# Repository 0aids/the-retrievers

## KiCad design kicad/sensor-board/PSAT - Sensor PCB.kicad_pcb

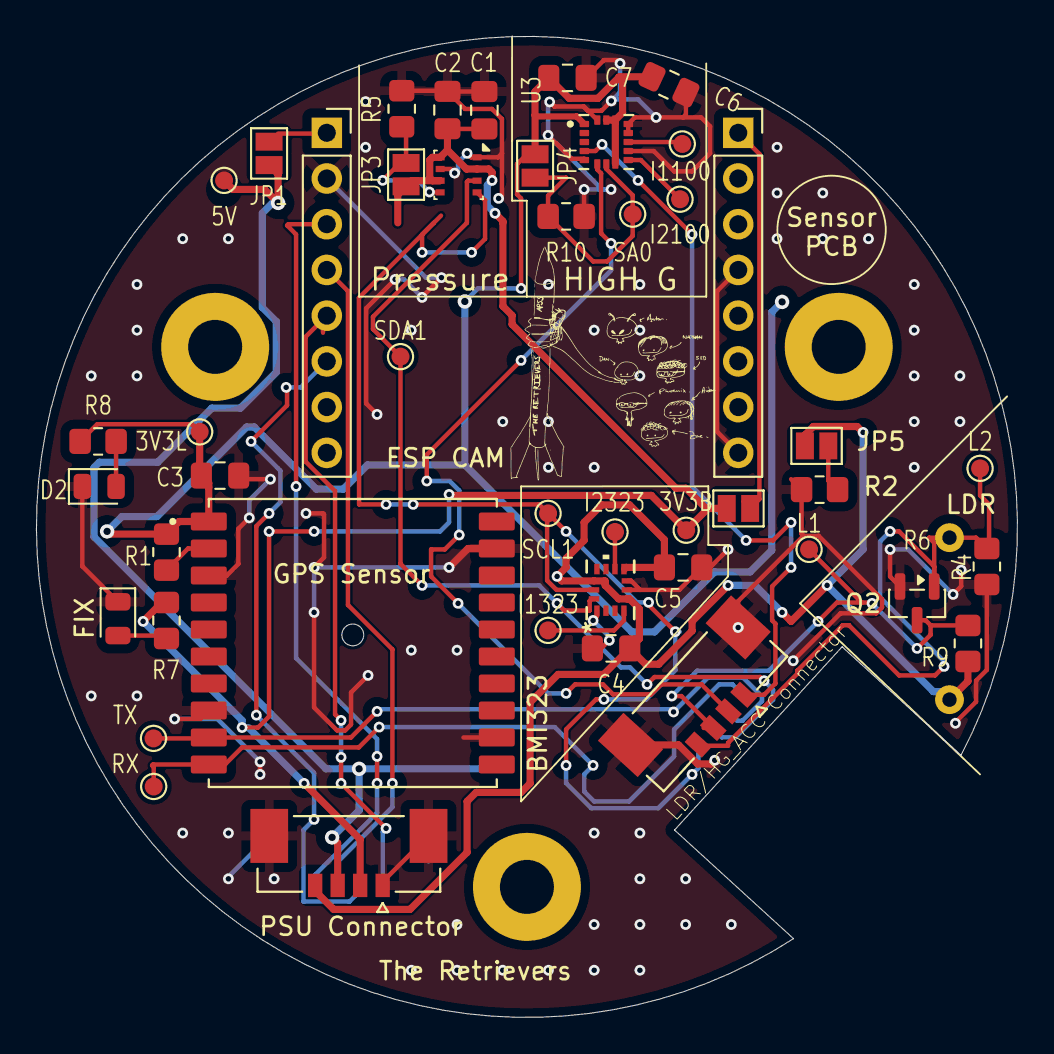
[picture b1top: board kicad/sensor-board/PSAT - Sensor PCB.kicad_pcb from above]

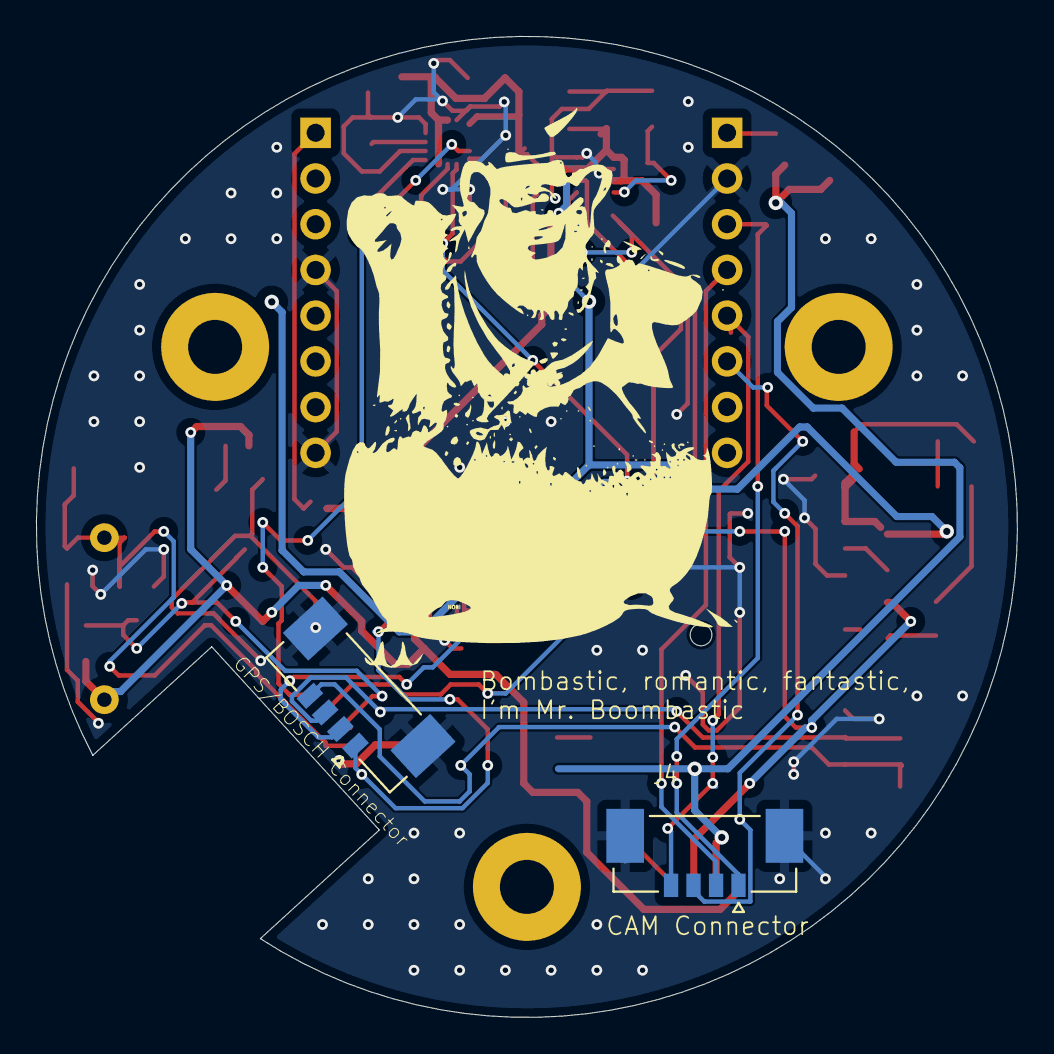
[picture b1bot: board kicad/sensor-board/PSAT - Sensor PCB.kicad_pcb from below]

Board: 2 copper layers, 54.5 x 54.5 mm, 50 parts (2 on the bottom side), 28 nets.

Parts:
3V3B, 3V3L, 5V: TestPoint; TestPoint_Pad_D1.0mm
C1, C2, C4, C5, C7: 100nF; C_0805_2012Metric_Pad1.18x1.45mm_HandSolder
C3: 22uF; C_0805_2012Metric_Pad1.18x1.45mm_HandSolder
C6: 10uF; C_0805_2012Metric_Pad1.18x1.45mm_HandSolder
D1, D2: LED; LED_0805_2012Metric
H1, H2, H3: MountingHole; MountingHole_3mm_Pad
I1100, I1323, I2100, I2323: TestPoint; TestPoint_Pad_D1.0mm
J1, J2, J3, J4: 533980471; MOLEX_533980471
JP1, JP2, JP3, JP4, JP5: EN_5; SolderJumper-2_P1.3mm_Open_Pad1.0x1.5mm
L1, L2: TestPoint; TestPoint_Pad_D1.0mm
Q2: Q_NPN_BEC; SOT-23
R1: 10k; R_0805_2012Metric_Pad1.20x1.40mm_HandSolder
R2, R5, R10: 1Meg; R_0805_2012Metric_Pad1.20x1.40mm_HandSolder
R4: 3.7k; R_0805_2012Metric_Pad1.20x1.40mm_HandSolder
R6: LDR07; ldr
R7, R8: 5.1k; R_0805_2012Metric_Pad1.20x1.40mm_HandSolder
R9: 100k; R_0805_2012Metric_Pad1.20x1.40mm_HandSolder
RX: TestPoint; TestPoint_Pad_D1.0mm
SA0: TestPoint; TestPoint_Pad_D1.0mm
SCL1: TestPoint; TestPoint_Pad_D1.0mm
SDA1: TestPoint; TestPoint_Pad_D1.0mm
TX: TestPoint; TestPoint_Pad_D1.0mm
U1: CD-PA1616D; XCVR_CD-PA1616D
U2: ESP32-CAM; ESPCam
U3: BME280; Bosch_LGA-8_2.5x2.5mm_P0.65mm_ClockwisePinNumbering
U4: BMI323; BMI323_BOS-M
U5: H3LIS100DLTR; PQFN50P300X300X100-16N

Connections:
3V3_BUCK: 3V3B.1, C1.2, C2.1, J3.2, JP2.1 (A), JP3.1 (A), R7.1, U3.2 (CSB), U3.6 (VDDIO), U3.8 (VDD)
3V3_LDO: 3V3L.1, C3.1, C4.2, C5.1, C6.1, C7.1, J3.4, JP4.1 (A), JP5.1 (A), R1.1, R6.1, R8.1, R9.2, U1.1 (VCC), U4.5 (VDDIO), U4.8 (VDD), U4.12 (CSB), U5.1 (VDD_IO), U5.8 (CS), U5.14 (VDD), U5.15 (VDD__1)
5V: 5V.1, J3.3, JP1.1 (A)
CAM_IO14: J4.3, U2.6 (IO14)
CAM_IO15: J4.4, U2.5 (IO15)
CAM_RX: J4.1, U2.3 (IO12)
CAM_TX: J4.2, U2.4 (IO13)
GND: C1.1, C2.2, C3.2, C4.1, C5.2, C6.2, C7.2, D1.1 (K), D2.1 (K), J1.S1 (SHIELD1), J1.S2 (SHIELD2), J2.S1 (SHIELD1), J2.S2 (SHIELD2), J3.1, J3.S1 (SHIELD1), J3.S2 (SHIELD2), J4.S1 (SHIELD1), J4.S2 (SHIELD2), Q2.2 (E), R2.2, R4.1, R5.2, R10.2, U1.3 (GND), U1.8 (GND), U1.12 (GND), U1.19 (GND), U2.2 (GND), U2.12 (GND.), U2.16 (.GND), U3.1 (GND), U3.7 (GND), U4.1 (SDO), U4.6 (GNDIO), U4.7 (GND), U5.5 (GND), U5.10 (GND__1), U5.12 (GND__2), U5.13 (GND__3), U5.16 (GND__4)
GPS_UART_RX: J2.4, RX.1, U1.10 (RX)
GPS_UART_TX: J2.3, TX.1, U1.9 (TX)
IN2_100: I2100.1, U5.9 (INT2)
INT1_100: I1100.1, U5.11 (INT1)
INT1_323: I1323.1, U4.4 (INT1)
INT2_323: I2323.1, U4.9 (INT2)
LIGHT1: J1.3, L1.1, Q2.3 (C), R9.1
LIGHT2: J1.4, L2.1, Q2.1 (B), R4.2, R6.2
unnamed: D1.2 (A), R7.2
unnamed: D2.2 (A), R8.2
unnamed: JP1.2 (B), U2.1 (5V)
unnamed: JP2.2 (B), U2.9 (3V3)
unnamed: R1.2, U1.2 (~RESET)
PRESSURE_ADDR: JP3.2 (B), R5.1, U3.5 (SDO)
SA0: JP4.2 (B), R10.1, SA0.1, U5.7 (SDO/SA0)
SCL1: J2.1, SCL1.1, U3.4 (SCK), U4.13 (SCX)
SCL2: J1.1, U5.4 (SCL/SPC)
SDA1: J2.2, SDA1.1, U3.3 (SDI), U4.14 (SDX)
SDA2: J1.2, U5.6 (SDA/SDI/SDO)
SDO: JP5.2 (B), R2.1

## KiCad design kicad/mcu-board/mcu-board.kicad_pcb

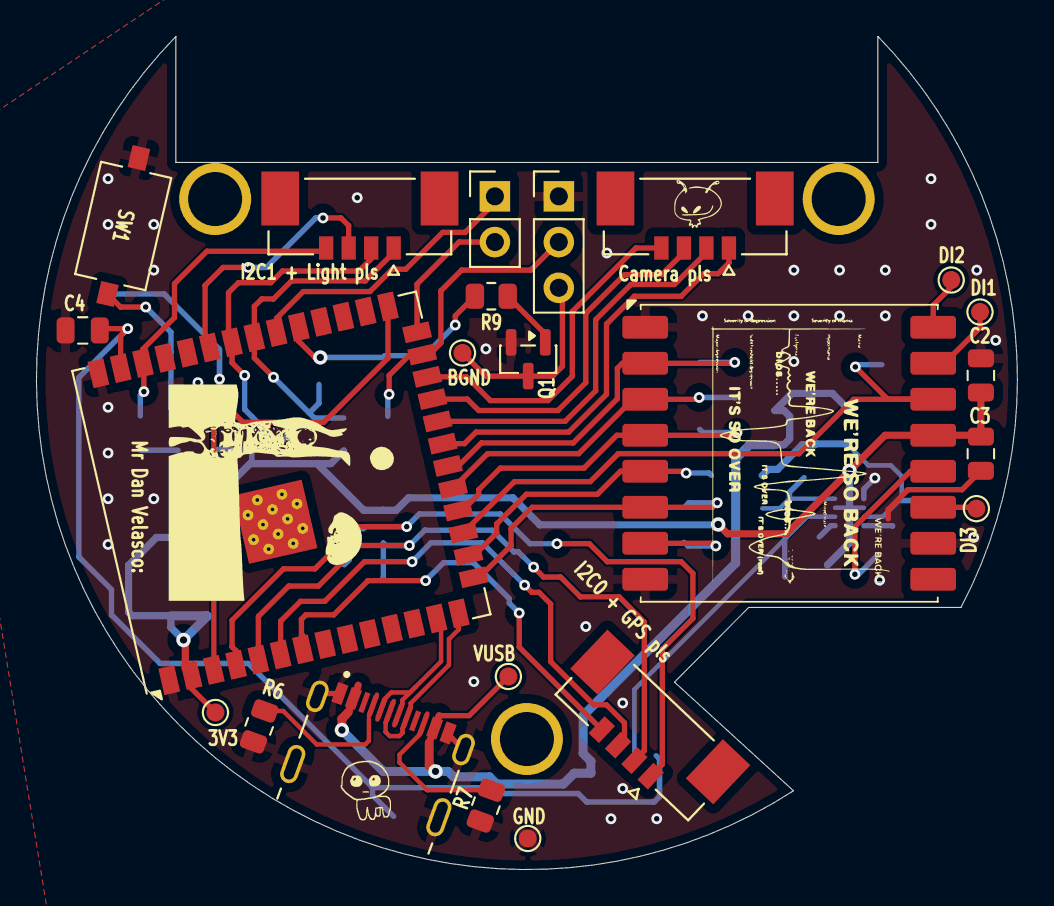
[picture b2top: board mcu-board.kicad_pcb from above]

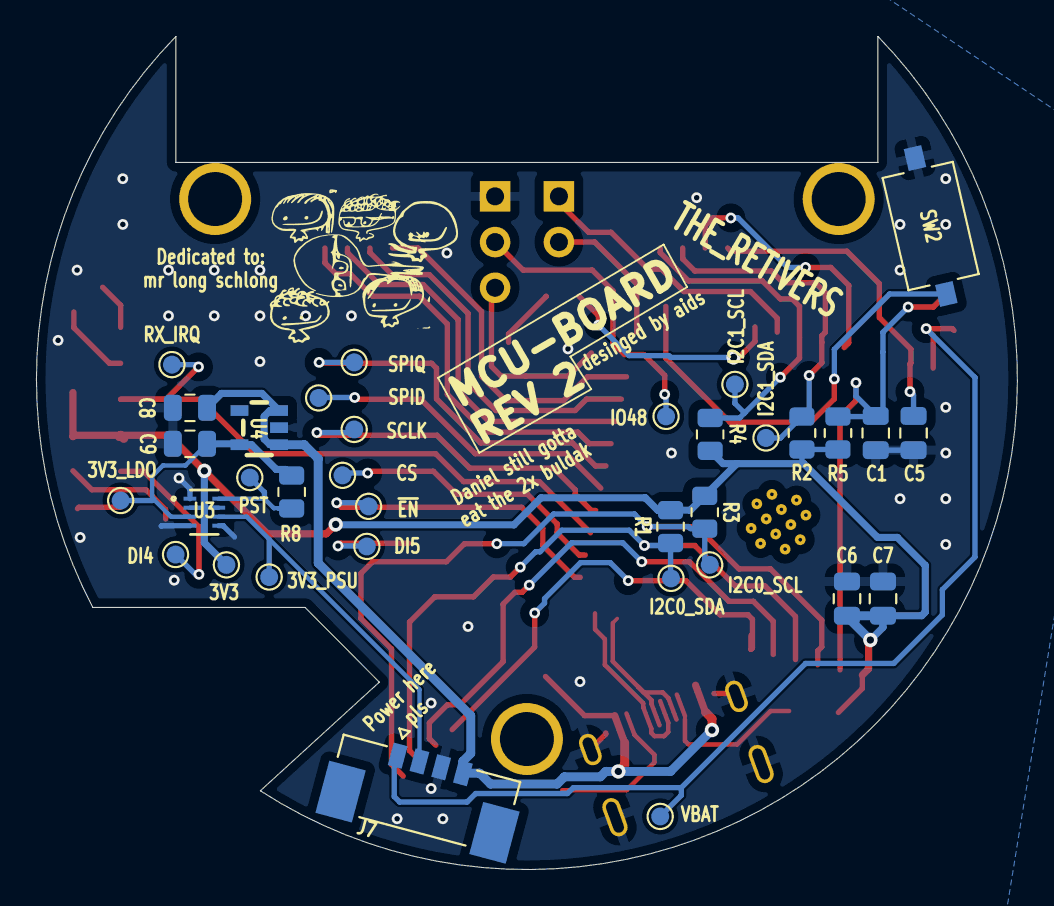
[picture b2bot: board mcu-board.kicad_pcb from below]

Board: 2 copper layers, 54.5 x 46.3 mm, 60 parts (34 on the bottom side), 42 nets.

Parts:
C1: 1uf; C_0805_2012Metric
C2, C6: 22uf; C_0805_2012Metric
C3, C4, C5, C7: 0.1uf; C_0805_2012Metric
C8, C9: 1u; C_0805_2012Metric
H1, H2, H3: MountingHole; Mounting-Hole-3mm-0.05mm-pad
J1: Conn_01x03; PinHeader_1x03_P2.54mm_Vertical
J2: Conn_01x02; PinHeader_1x02_P2.54mm_Vertical
J3, J4, J5, J7: 533980471; MOLEX_533980471
J6: UJ20-C-H-G-SMT-P16-TR; SAMESKY_UJ20-C-H-G-SMT-P16-TR
Q1: MMBT619; SOT-23
R1, R2, R3, R4, R6, R7, R8: 5.1k; R_0805_2012Metric
R5, R9: 10k; R_0805_2012Metric
SW1, SW2: SW_Push; SW_Tactile_SPST_NO_Straight_CK_PTS636Sx25SMTRLFS
TP1, TP2, TP3, TP4, TP5, TP6, TP7, TP8, TP9, TP10, TP11, TP12, TP13, TP14, TP15, TP15#2, TP16, TP17, TP18, TP19, TP20, TP21, TP22, TP23: TestPoint; TestPoint_Pad_D1.0mm
U1: Lora1276-C1-868
U2: ESP32-S3-WROOM-1U-N16R8; ESP32-S3-WROOM-1U
U3: LM66200DRLR; SOT-5X3_DRL_TEX
U4: TLV75733PDBVR
VBAT1: TestPoint; TestPoint_Pad_D1.0mm

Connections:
+3V3: C2.1, C3.1, C6.1, C7.1, R1.2, R2.2, R3.1, R4.1, R5.2, TP15.1, TP19.1, U1.13 (VCC), U2.2 (3V3), U3.2 (VOUT), U3.7 (VOUT)
+3V3_LDO_LOCAL: C9.2, R8.1, TP21.1, U3.3 (VIN1), U4.5 (OUT)
+3V3_PSU_LDO: J7.2, TP22.1, U3.6 (VIN2)
/BUZZER_IO38: R9.1, U2.31 (IO38)
/CAM_IO13: J5.1, U2.21 (IO13)
/CAM_IO14: J5.2, U2.22 (IO14)
/CAM_IO21: J5.3, U2.23 (IO21)
/CAM_IO47: J5.4, U2.24 (IO47)
/D+: J6.A6 (DP1), J6.B6 (DP2), U2.14 (IO20)
/D-: J6.A7 (DN1), J6.B7 (DN2), U2.13 (IO19)
/DI1: TP11.1, U1.15 (DI1)
/DI2: TP12.1, U1.16 (DI2)
/DI3: TP13.1, U1.11 (DI3)
/DI4: TP14.1, U1.12 (DI4)
/DI5: TP15#2.1, U1.7 (DI5)
/ESP_RESET: C1.1, R5.1, SW1.2, U2.3 (EN)
/GPS_U1RX_IO7: J3.4, U2.7 (IO7)
/GPS_U1TX_IO6: J3.3, U2.6 (IO6)
/I2C0_SCL_IO4: J3.1, R3.2, TP4.1, U2.4 (IO4)
/I2C0_SDA_IO5: J3.2, R1.1, TP2.1, U2.5 (IO5)
/I2C1_SCL_IO40: J4.1, R4.2, TP5.1, U2.33 (IO40)
/I2C1_SDA_IO41: J4.2, R2.1, TP3.1, U2.34 (IO41)
/IO39: J2.1, U2.32 (IO39)
/IO45: J2.2, U2.26 (IO45)
/LIGHT_1_IO42: J4.3, U2.35 (IO42)
/LIGHT_2_ADC1CH1_IO2: C5.2, J4.4, U2.38 (IO2)
/LORA_IRQ_IO9: TP16.1, U1.14 (DI0), U2.17 (IO9)
/LORA_SPI3_CLK_IO10: TP9.1, U1.4 (SCK), U2.18 (IO10)
/LORA_SPI3_CS_IO46: TP10.1, U1.5 (~SS), U2.16 (IO46)
/LORA_SPI3_D_IO11: TP8.1, U1.3 (MOSI), U2.19 (IO11)
/LORA_SPI3_Q_IO12: TP7.1, U1.2 (MISO), U2.20 (IO12)
/Power Management/POWER_ST: R8.2, TP20.1, U3.8 (ST)
/SERVO_IO48: J1.2, TP6.1, U2.25 (IO48)
/VBAT_IO1: C4.1, J7.1, U2.39 (IO1), VBAT1.1
/~LORA_EN_IO3: TP1.1, U1.6 (~RESET), U2.15 (IO3)
BUZ_GND: J1.3, Q1.3 (C), TP23.1
GND: C1.2, C2.2, C3.2, C4.2, C5.1, C6.2, C7.2, C8.1, C9.1, J1.1, J6.A1_B12 (GND), J6.A12_B1 (GND__1), J6.SH1 (SHIELD), J6.SH2 (SHIELD__1), J6.SH3 (SHIELD__2), J6.SH4 (SHIELD__3), J7.3, Q1.2 (E), R6.1, R7.1, SW1.1, SW2.1, TP18.1, U1.1 (GND), U1.8 (GND), U1.10 (GND), U2.1 (GND), U2.40 (GND), U3.1 (GND), U3.4 (~ON), U3.5 (GND), U4.2 (GND)
unnamed: J6.A5 (CC1), R6.2
unnamed: J6.B5 (CC2), R7.2
unnamed: Q1.1 (B), R9.2
unnamed: SW2.2, U2.27 (IO0)
V_USB: C8.2, J6.A4_B9 (VBUS), J6.A9_B4 (VBUS__1), J7.4, TP17.1, U4.1 (IN), U4.3 (EN)

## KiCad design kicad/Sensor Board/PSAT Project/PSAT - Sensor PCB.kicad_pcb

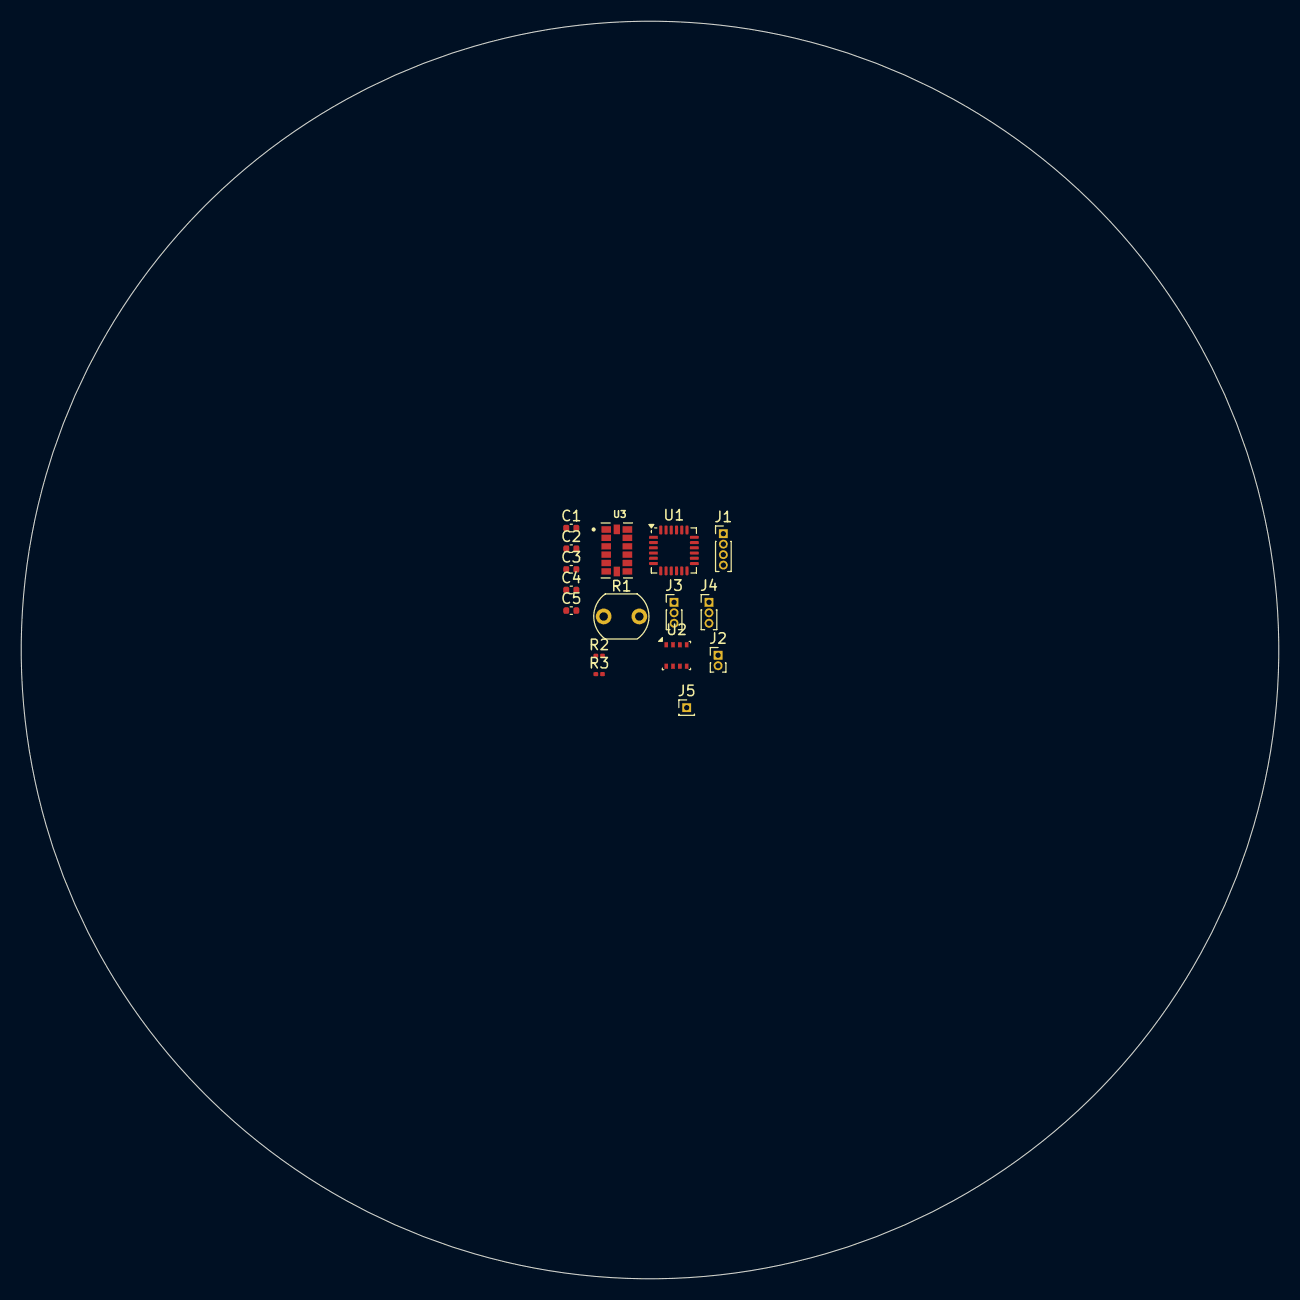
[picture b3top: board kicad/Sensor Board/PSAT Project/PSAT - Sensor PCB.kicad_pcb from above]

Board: 2 copper layers, 120.0 x 120.0 mm, 16 parts (0 on the bottom side), 16 nets, no tracks yet.

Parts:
C1: 2.2n; C_0402_1005Metric
C2: 0.1n; C_0402_1005Metric
C3: 0.1μ; C_0402_1005Metric
C4, C5: 100n; C_0402_1005Metric
J1: MCU Conn_01x04; PinHeader_1x04_P1.00mm_Vertical
J2: Conn_01x02; PinHeader_1x02_P1.00mm_Vertical
J3, J4: Conn_01x03; PinHeader_1x03_P1.00mm_Vertical
J5: Conn_01x01; PinHeader_1x01_P1.00mm_Vertical
R1: LDR07; R_LDR_5.1x4.3mm_P3.4mm_Vertical
R2, R3: 4.7k; R_0201_0603Metric
U1: MPU-6000; InvenSense_QFN-24_4x4mm_P0.5mm
U2: BME280; Bosch_LGA-8_2.5x2.5mm_P0.65mm_ClockwisePinNumbering
U3: PQFN80P500X300X100-14N

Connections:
+3.3V: C2.1, C4.1, R1.1, U1.8 (~CS), U1.13 (VDD), U2.8 (VDD), U3.3 (RESERVED), U3.6 (Vs)
GND: C1.1, C2.2, C3.1, C4.2, C5.2, J5.1, R1.2, U1.1 (CLKIN), U1.11 (FSYNC), U1.18 (GND), U2.1 (GND), U2.5 (SDO), U2.7 (GND), U3.2 (GND), U3.4 (GND), U3.5 (GND), U3.11 (RESERVED), U3.12 (SDO/ALT_ADDRESS)
unnamed: J1.1, U1.23 (SCL/SCLK)
unnamed: J1.2, U1.9 (AD0/MISO)
unnamed: J1.3, U1.24 (SDA/MOSI)
unnamed: J1.4, U1.12 (INT)
unnamed: C5.1, J2.1, J2.2, R2.1, R3.1, U2.3 (SDI), U2.4 (SCK), U2.6 (VDDIO)
unnamed: J3.1, U3.8 (INT1)
unnamed: J3.2, U3.9 (INT2)
unnamed: J3.3, U3.10 (NC)
unnamed: J4.1, U3.14 (SCL/SCLK)
unnamed: J4.2, U3.13 (SDA/SDI/SDIO)
unnamed: J4.3, U3.7 (CS)
unnamed: C1.2, U1.20 (CPOUT)
unnamed: C3.2, U1.10 (REGOUT)
unnamed: R2.2, R3.2, U2.2 (CSB)

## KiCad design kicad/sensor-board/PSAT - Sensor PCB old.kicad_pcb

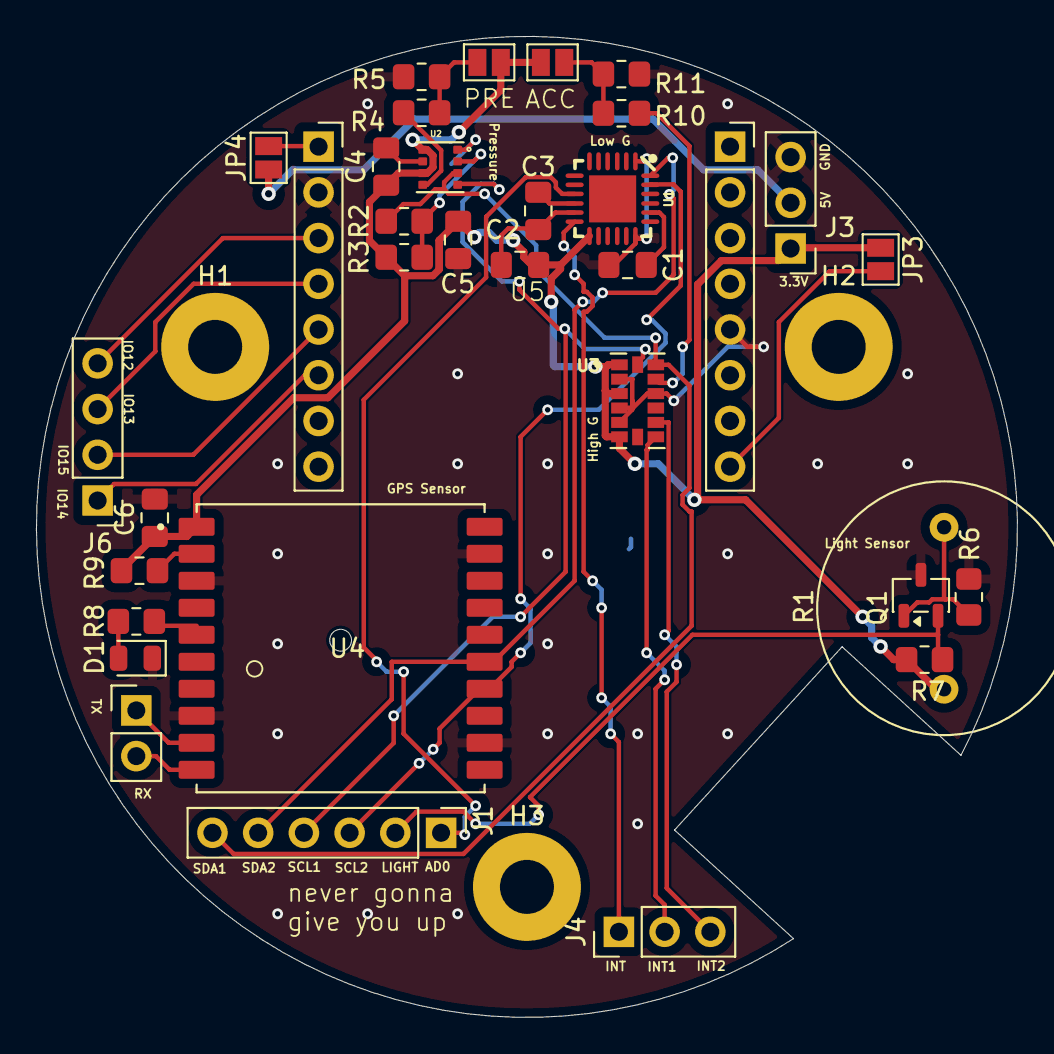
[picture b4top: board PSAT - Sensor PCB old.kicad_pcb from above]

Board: 2 copper layers, 54.5 x 54.5 mm, 36 parts (0 on the bottom side), 31 nets.

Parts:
C1: 2.2n; C_0805_2012Metric_Pad1.18x1.45mm_HandSolder
C2: 0.1n; C_0805_2012Metric_Pad1.18x1.45mm_HandSolder
C3: 0.1μ; C_0805_2012Metric_Pad1.18x1.45mm_HandSolder
C4, C5: 100n; C_0805_2012Metric_Pad1.18x1.45mm_HandSolder
C6: 22uF; C_0805_2012Metric_Pad1.18x1.45mm_HandSolder
D1: LED; LED_0805_2012Metric
H1, H2, H3: MountingHole; MountingHole_3mm_Pad
J1: Conn_01x06; PinHeader_1x06_P2.54mm_Vertical
J2: Conn_01x02; PinHeader_1x02_P2.54mm_Vertical
J3: Conn_01x03_Pin; PinHeader_1x03_P2.54mm_Vertical
J4: Conn_01x03; PinHeader_1x03_P2.54mm_Vertical
J6: MCU - Conn_01x04; PinHeader_1x04_P2.54mm_Vertical
JP1, JP2, JP3, JP4: EN_5; SolderJumper-2_P1.3mm_Open_Pad1.0x1.5mm
Q1: Q_NPN_BCE; SOT-23-3
R1: LDR07; R_LDR_D13.8mm_P9.0mm_Vertical
R2, R3: 4.7k; R_0805_2012Metric_Pad1.20x1.40mm_HandSolder
R4, R10: 1k5; R_0805_2012Metric_Pad1.20x1.40mm_HandSolder
R5, R11: 1Meg; R_0805_2012Metric_Pad1.20x1.40mm_HandSolder
R6, R7: 10k; R_0805_2012Metric_Pad1.20x1.40mm_HandSolder
R8: 1k; R_0805_2012Metric_Pad1.20x1.40mm_HandSolder
R9: 180k; R_0805_2012Metric_Pad1.20x1.40mm_HandSolder
U1: MPU-6000; QFN-24-EP
U2: BME280; PSON65P250X250X100-8N
U3: ADXL375; PQFN80P500X300X100-14N
U4: CD-PA1616D; XCVR_CD-PA1616D
U5: ESP32-CAM; ESPCam

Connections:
3.3V: C2.1, C4.1, C5.1, C6.1, J3.1, JP1.1 (A), JP2.1 (A), JP3.1 (A), R1.1, R3.1, R7.2, R9.1, U1.13 (VDD), U2.6 (VDDIO), U2.8 (VDD), U3.1 (VDD_I/o), U3.3 (RESERVED), U3.6 (Vs), U4.1 (VCC)
5V: J3.2, JP4.1 (A)
/GPS Reset: R9.2, U4.2 (~RESET)
ADO: J1.1, U1.9 (AD0/MISO)
GND: C1.1, C2.2, C3.1, C4.2, C5.2, C6.2, D1.1 (K), J3.3, Q1.3 (E), R5.2, R6.1, R11.2, U1.1 (CLKIN), U1.11 (FSYNC), U1.18 (GND), U2.1 (GND), U2.7 (GND), U3.2 (GND), U3.4 (GND), U3.5 (GND), U3.11 (RESERVED), U4.3 (GND), U4.8 (GND), U4.12 (GND), U4.19 (GND), U5.2 (GND), U5.13 (GND.)
GPS_UART_RX: J2.2, U4.10 (RX)
GPS_UART_TX: J2.1, U4.9 (TX)
INT: J4.1, U1.12 (INT)
LIGHT: J1.2, Q1.2 (C), R7.1
unnamed: D1.2 (A), R8.2
unnamed: J4.2, U3.8 (INT1)
unnamed: J4.3, U3.9 (INT2)
unnamed: J6.1, U5.6 (IO14)
unnamed: J6.2, U5.5 (IO15)
unnamed: J6.3, U5.4 (IO13)
unnamed: J6.4, U5.3 (IO12)
unnamed: JP1.2 (B), R4.2, R5.1
unnamed: JP2.2 (B), R10.2, R11.1
unnamed: JP3.2 (B), U5.16 (3V3)
unnamed: JP4.2 (B), U5.1 (5V)
unnamed: Q1.1 (B), R1.2, R6.2
unnamed: C1.2, U1.20 (CPOUT)
unnamed: C3.2, U1.10 (REGOUT)
unnamed: R2.2, R3.2, U2.2 (CSB)
unnamed: R8.1, U4.5 (3D-FIX)
SCL1: J1.4, U2.4 (SCK), U3.14 (SCL/SCLK)
SCL2: J1.3, U1.23 (SCL/SCLK), U4.14 (RX1/I2C_SCL)
SDA1: J1.6, R2.1, U2.3 (SDI), U3.13 (SDA/SDI/SDIO)
SDA2: J1.5, U1.24 (SDA/MOSI), U4.15 (TX1/I2C_SDA)
SDO_ACC: R10.1, U3.12 (SDO/ALT_ADDRESS)
SDO_PRESSURE: R4.1, U2.5 (SDO)

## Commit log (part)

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2026-01-13 feat: reuseable button component
2026-01-13 chore: rename lowpwr to lowPower, just looked weird
2026-01-13 chore: update cspell ignore list
2026-01-13 chore: use uart num from config for gps
2026-01-14 feat: new deployPending state
2026-01-14 feat: add task to check ADC to confirm deployment
2026-01-14 feat: buzzer working
2026-01-14 fix: include if global event in config for timer
2026-01-15 refactor: ldr.c & ldr.h are now in the code style Aiden sent
2026-01-15 fix: removed the static variables adcRaw & voltage while removing the 2d matrix.
2026-01-15 style: Added comments to ldr.h
2026-01-17 chore: update baud rate for new gps chip
2026-01-17 fix: Fixed some syntax erorrs and reverted changes in psat station
2026-01-17 test: Added preflight tests for both ldr and battery
2026-01-18 feat: convert shared/ into a esp component This is so that we can use shared_state.c in any component
2026-01-18 chore: update currentState_s to use psat_globalState.currentFSMState
2026-01-18 feat: simple buzzer beep test
2026-01-18 test: buzzer gpio pin goes HIGH during beep
2026-01-18 test: add tests for the servo
2026-01-18 chore: moved the idf.py flakes to the relevant psat-station subproject
2026-01-18 feat: added the shared_lora as a component named "lora"
2026-01-18 refac: Separated lora config from loraImpl.h into loraCfg.h.
2026-01-18 revert: "feat: update gpsData_s to psat_globalState.gpsData"
    This reverts commit 50d5446f3d3b955fb7a0421dd1cfc662480110d1.
2026-01-18 fix: precommit to work without using espidf terminal
2026-01-19 revert: undid some formatting done at 8f58e9f3.
2026-01-19 chore: added ai disclosure for tests
2026-01-19 fix: Added proper error handling, will add some checker in the implementation later
2026-01-19 feat: add entry, exit handlers for each state
2026-01-19 test: added the files for testing ldr
2026-01-19 feat: actually update the entry/exit handlers to contain what used to be in state_handlers.c
2026-01-19 feat: added the tests for ldr and made sure it builds
2026-01-19 fix: istg I pushed this and it fucking disappeared - fixed precommit
2026-01-21 fix(#13): Stop using goofy struct for config and just use #define And also format everything
2026-01-21 chore: remove random main.c file
2026-01-21 fix: reduced stack usage by decreasing default packet size. Will switch to heap allocation later.
    no more stack overflows now
2026-01-21 fix: for some reason was using a copy of shared_lora.h, not a symlink.
2026-01-21 feat: implemented internal use dynamic memory allocation for loraFsm.
2026-01-22 fix: clashing gpio_install_isr_service between lora and buttons. Moved to prelaunch entry handler
2026-01-22 refactor: moved configuration of ldr and renamed unclear variables
2026-01-23 fix: forgot to merge a stash for pin config
2026-01-23 chore: create subproject for parsing data from the ai-thinker to the computer for python
2026-01-24 test: changed the ldr tests to use multiple buffers instead of the same one.
2026-01-24 feat: add fastapi boilerplate
2026-01-24 feat: add loraImpl library for use in C
2026-01-24 feat: add leaflet js library locally
2026-01-24 feat: add StateManager
2026-01-24 feat: log access if 'log' is passed to end
2026-01-24 feat: very basic html
2026-01-24 test: changed the ldr testing to use multiple buffer instead of sharing the same buffer
2026-01-24 fix: penix forgot to add some #includes for ldr
2026-01-24 fix: ldr import issues again
2026-01-24 feat: added drivers for sensor board sensors
2026-01-24 refactor(ldr): Replaced the esp error checking system with our custom one.
2026-01-24 feat: use vite to bundle js files together making it easier to use multiple files for this project
2026-01-25 fix: Removed -Wno-implicit-function-defintions and fixed relevant ldr.c file. Add placeholders for header only libs.
2026-01-25 chore: update variable names and paths after that vite change i made earlier
2026-01-25 feat: update to send data over lora as well
2026-01-25 fix: partial fix to uart not completely receiving on the ai-thinker
2026-01-26 refac: move some of the frontend functions out into their own files
2026-01-26 fix: dont send footer in lora send
2026-01-26 chore: lil bitty fsm text change
2026-01-26 fix: buzzer global event, ldr imports, buttons enabled
2026-01-26 new symbols & footprints for connectors and usb-c
2026-01-26 feat: send pong back
2026-01-26 feat: send buzzer beep request on the button
2026-01-26 feat: Completed sensor board
2026-01-26 feat: Changed labels & started pcb wiring
2026-01-26 feat: show lora stats and other gps data on ui
2026-01-26 feat: Changed ESP32 connectors
2026-01-26 feat: init servo on boot rather than after prelaumch
2026-01-26 fix: show packets recieved on ui
2026-01-27 feat: Added 3V3_LDO LED and changed power labels
2026-01-27 pcb: added the LDO to the library
2026-01-27 chore: sync branch with master
2026-01-27 feat: complete psu schematic (not sure about the 2 extra pins on the headers though)
2026-01-29 feat: replaced old connectors to 533980471
2026-01-29 feat: Gps changed to BMI323
2026-01-30 feat: separated pressure and temperature functions (Aiden is bullying me)
2026-01-30 fix: Aiden made it work IDK how or what he did
2026-01-30 feat: Wiring sensor board, incomplete
2026-01-31 feat: added high g accel foot/sym
2026-01-31 feat: Wiring PCB adding silkscreen
2026-01-31 feat: Aidan review this: fixed righted angle wires
2026-02-01 feat: added improvements and removed irrelevant components
2026-02-01 feat: ART
2026-02-01 chore: reduce thickness to be same as other boards
2026-02-02 chore: add namespace for err things and rearange shared_state file
2026-02-07 feat: add enum for component
2026-02-08 feat: add component, error structs and componentStatus
2026-02-08 feat: initall components function as im lazy
2026-02-08 chore: woopsie some of my snake case crept in mbmb
2026-02-08 feat: add function to get compoennt
2026-02-08 style: format everything
2026-02-10 chore: woopsie daisies spelling mistake cspell wouldnt havelet this happen
2026-02-10 chore: forgor header guard :skull:
2026-02-10 feat: move registering components to its own file
2026-02-10 feat: deinit for gps
2026-02-10 fix: debug e revealed uart_flush is fucking broken (idk why i spent 30min on this alone :sob:)
2026-02-10 feat: pin tasks to specific cores
2026-02-14 fix: use task notifications to kill gps task more faster
2026-02-15 feat: print queue items and drop timer events when in error state
2026-02-15 feat: looks like a simple bool is all you need to fix the gps task issue
2026-02-15 fix: 20s is too low, in fact it would never be reached due to backoff
2026-02-15 refac: use new component method for init/deinit/starting/stopping LDR
2026-02-15 fix: warning due to tag being in header file
2026-02-15 chore: POST EVENT SHUT THE FUCK UP
2026-02-16 fix: make the fuckass cmakelists extension happy
2026-02-17 fix: forgor to create the mutex :skull:
2026-02-17 chore: remove the random test function i had there
2026-02-17 feat: buzzer deinit
2026-02-17 feat: store the previous state
2026-02-17 chore: update spreading factor to 8
2026-02-18 revert: sync word not needed to be changed
2026-02-18 revert: literally any change ive made to lora since CDR
2026-02-18 feat: Wrote code that takes a picture with the camera every 5 seconds
2026-02-18 refac: changed the error handling for BMP280
2026-02-18 refac: no more magic number for servo
2026-02-18 feat: implement requests for ones already existing
2026-02-18 refac: minor tweaks to bmp280 error handling and up dated gps, buzzers, timers error handling to use psatErr_postError
2026-02-18 feat: check we recieved pong
2026-02-18 fix: oopsies i was editing a copy
2026-02-18 feat: call disable component on premanent error
2026-02-18 fix: yet another forgotten break
2026-02-18 feat: enable/disable component requests
2026-02-19 feat: added buzzer preflightTest() function
2026-02-20 fea/fix: added timer preflightTest and fixed bug causing a crash whenever a preflightTest was called
2026-02-20 refac:updated LDR preflight test
2026-02-20 chore: delete old files for react migration
2026-02-20 feat: main html file
2026-02-20 feat: function to fetch data from api
2026-02-20 feat: boilerplate for react app
2026-02-20 feat: commands component (non functional just ui)
2026-02-20 chore: get rid of eslint it lowkey pmo fuck off, eslint i hate you with passion you make my life sad and missrible idk how to even spell (cspell probably does)
2026-02-20 feat: finish leaflet map part of the ui :D
2026-02-20 feat: added get data and reset functions for bmi323 and other random stuff
2026-02-21 feat: made prelaunch results get transmited by lora maybe
2026-02-21 refac: state.gps -> state.data.gps + other data now too
2026-02-21 feat: update state to be same as frontend, also fancy decorator
2026-02-21 feat: show the last packet timestamp in a human readable way
2026-02-21 feat: sending commands all working (have hard coded values for stuff that require options eg enable/disable components and state forwad)
2026-02-22 chore: vscode keeps changing cmakelists it might as well
2026-02-23 fix: remove lora has malloc definiton as null
2026-02-23 fix: make threads timeout when ctrl c and update baud rate
2026-02-23 fix: idk where the curly braces despawned from
2026-02-23 fix: fixed issue with bmp280 preflight test
2026-02-23 fix: null check component.preflight, and use getComponent function rather than directly access, also add debug prints
2026-02-23 fix: move all component init to AFTER preflight tests to avoid crash
2026-02-23 fix: wait some time after kill task to wait for uart read bytes timeout to actuall occur and kill the task
2026-02-23 refactor: cleaned up main.c and moved uart functions to uart component
2026-02-23 feat: rewrite the order of the bits
2026-02-23 feat: show when no data yet, and strip namespace
2026-02-23 feat: update preflight data on receiving over lora all working :D
2026-02-23 chore: remove preflightSuccess/preflightFail packet types as preflightData alrady includes that information
2026-02-23 feat: include modal for component selection in prelaunch
2026-02-23 fix: bar should be above fuckass leaflet
2026-02-23 feat: started adding kalman filter
2026-02-24 feat: update pins for new pcb
2026-02-24 feat: pretty printing of stuff with rich panels
2026-02-25 feat: add component bit configs for enabled, inited, tasks and rewrite the functions to use them
2026-02-25 feat: Made code for taking pictures with the esp-cam.
2026-02-25 feat: add more packet types for tasks and mark requests
2026-02-25 feat: start/stop task & mark enable/disable component packets handlers
2026-02-25 fix: shit wasnt being enabled because i had the flag wrong way around oopsies, also add some printing
2026-02-26 feat: include more data in componentdata type
2026-02-26 feat: show if component enabled or not in prelaunch
2026-02-26 feat: show preflight result on ui
2026-02-26 feat: show number of tests passed
2026-02-26 chore: forgot title for start stop task modals
2026-02-28 feat: Now able to take pics from psat esp, but has to have slot_config.width = 4 for sdmmc_slot_config_t
2026-02-28 refactor: Moved pin defs to pin_config.h
2026-03-01 refactor: Changed the name of some functions/macros to match naming convention.
2026-03-01 feat: add function to convert gga to binary packet that psat ground wants
2026-03-02 refactor: Made many more functions for camera_control so it is easier to use
2026-03-04 test: created preflight tests for cam (WIP)
2026-03-04 chore: hide the fatass directory with the actual images
2026-03-04 fix: gps data gives us nan, however this is not encodable over json
2026-03-04 chore: simple spelling mistake cspell wouldve totally fixed (it wouldn't have :sob:)
2026-03-04 fix: dont send telemetry packet twice :sob:
2026-03-04 fix: ensure state we are transitioning to is not larger than max state
2026-03-04 fix: weird merge stuff idk
2026-03-04 feat: print out when we recieve an ack
2026-03-04 fix: forgot to add prelaunch commands
2026-03-04 test: Finished the preflight test for the camera module.
2026-03-04 test fix: used the wrong function to delete uart drivers
2026-03-04 test: fixed the test
2026-03-06 fix: reverted psat-station.c
